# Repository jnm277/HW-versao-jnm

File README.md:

# HW-versao-jnm
Minha versão dos módulos genéricos HW, todos os arquivos estão no repositório

# HW-764 (19/10)
É um regulador linear que converte 5v em 3.3v baseado no AMS1117.
Projetei essa pcb em uns 30 minutos.
## Renderização 3D:

## A pcb:

## A esquemática:

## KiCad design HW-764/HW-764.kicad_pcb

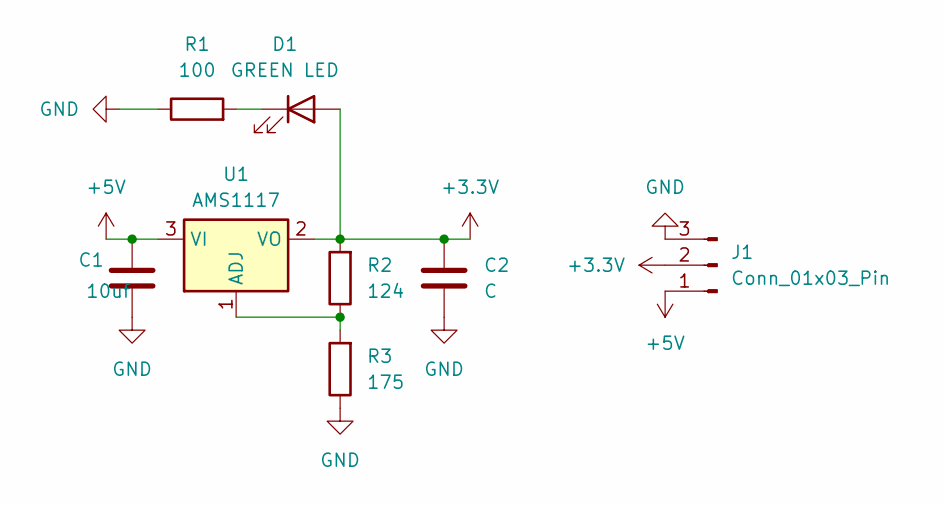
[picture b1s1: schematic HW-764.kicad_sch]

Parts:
C1: 10uf; C_0805_2012Metric_Pad1.18x1.45mm_HandSolder
C2: C; C_0805_2012Metric_Pad1.18x1.45mm_HandSolder
D1: GREEN LED; LED_0805_2012Metric_Pad1.15x1.40mm_HandSolder
J1: Conn_01x03_Pin; PinHeader_1x03_P2.54mm_Horizontal
R1: 100; R_0805_2012Metric_Pad1.20x1.40mm_HandSolder
R2: 124; R_0805_2012Metric_Pad1.20x1.40mm_HandSolder
R3: 175; R_0805_2012Metric_Pad1.20x1.40mm_HandSolder
U1: AMS1117; SOT-223-3_TabPin2

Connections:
+3.3V: C2.1, D1.2 (A), J1.2, R2.2, U1.2 (VO)
+5V: C1.1, J1.1, U1.3 (VI)
GND: C1.2, C2.2, J1.3, R1.1, R3.1
unnamed: D1.1 (K), R1.2
unnamed: R2.1, R3.2, U1.1 (ADJ)

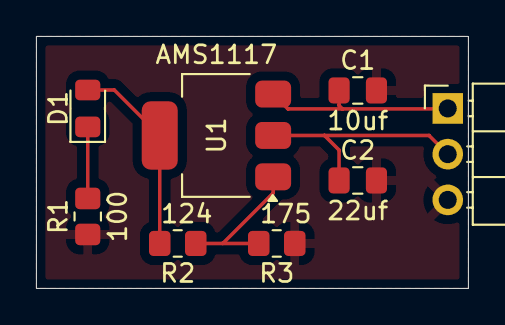
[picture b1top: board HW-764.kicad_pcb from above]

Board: 2 copper layers, 24.0 x 14.0 mm, 8 parts (0 on the bottom side), 5 nets.
